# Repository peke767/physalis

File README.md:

# Physalis

The Physalis is 75% Keyboard.  

## Part List

PCB --- 1 pcs  
RP2040 Zero --- 1 pcs  
Diode [1N4148 SMD] --- 82 pcs  
Hotswap Socket --- 82 pcs  
Switch --- 82/81 pcs  
2u Stabilizer --- 3 pcs  
6.25u or 7u or 6u Stabilizer --- 1 pcs

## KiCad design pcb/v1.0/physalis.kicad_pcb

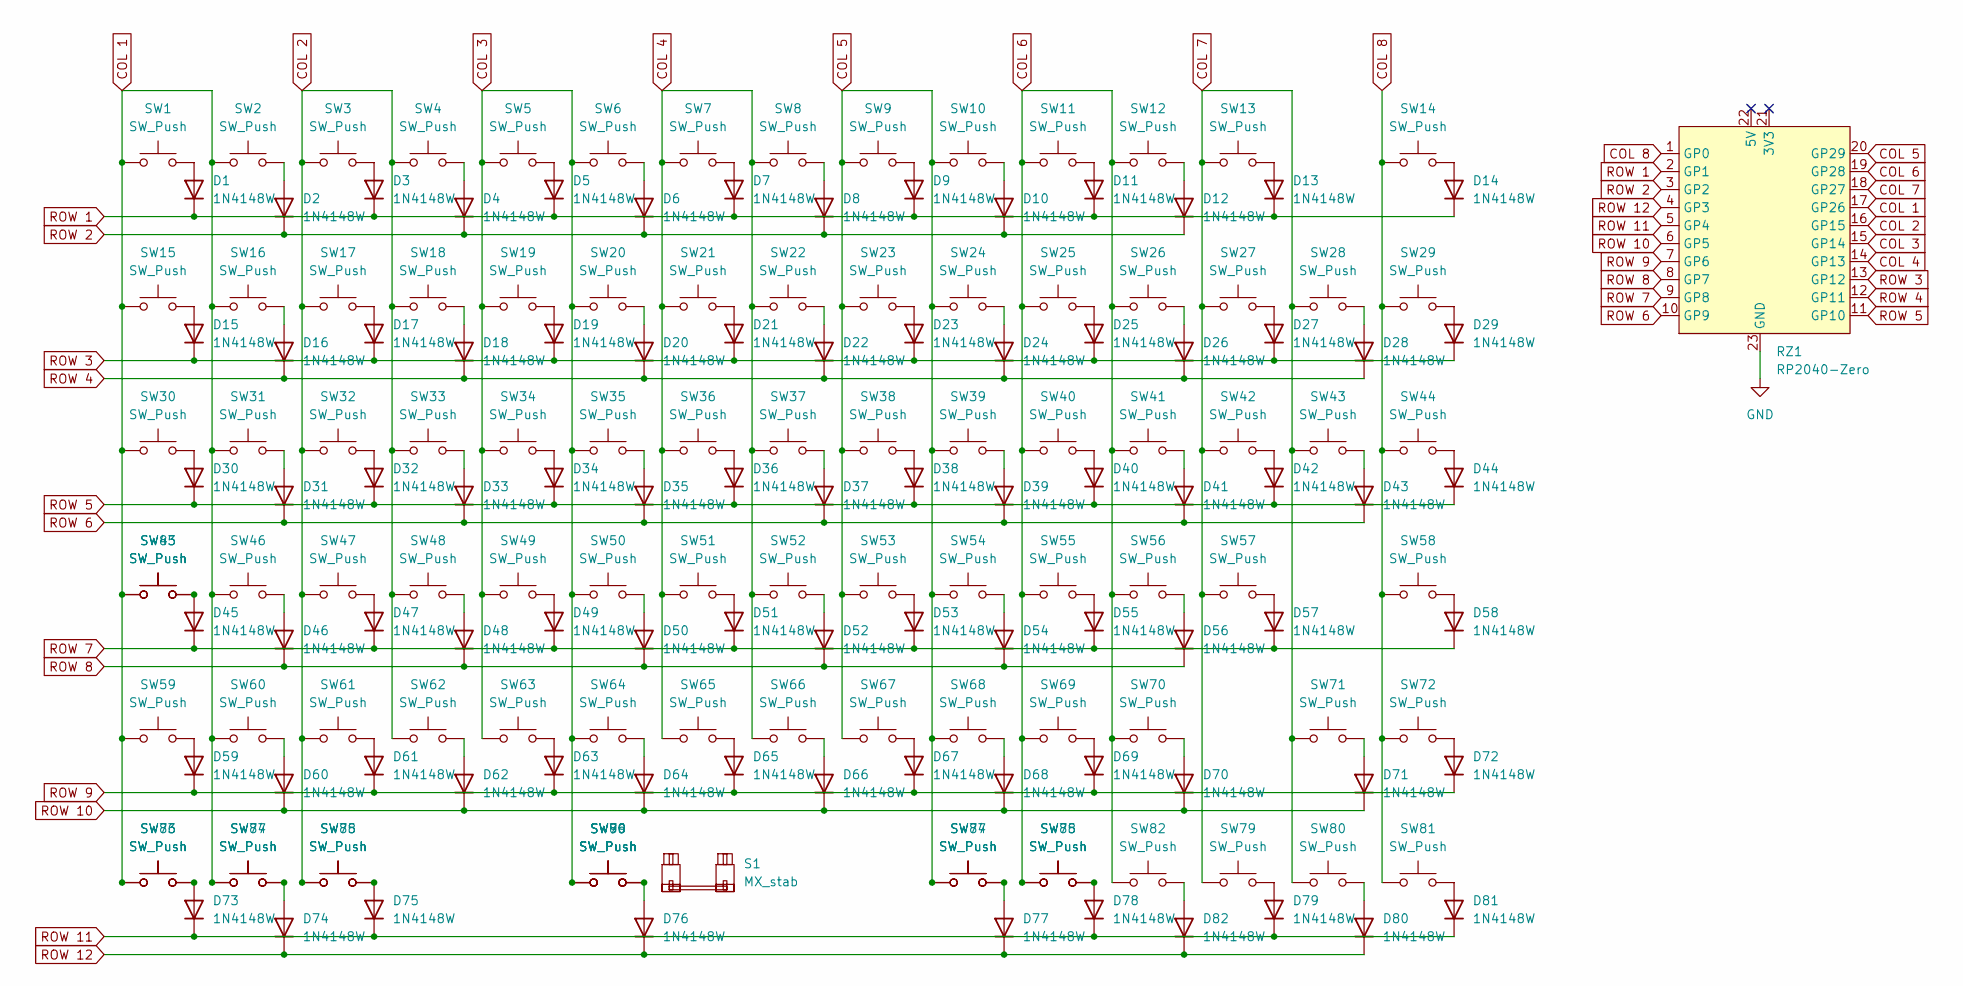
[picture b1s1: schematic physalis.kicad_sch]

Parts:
D1, D2, D3, D4, D5, D6, D7, D8, D9, D10, D11, D12, D13, D14, D15, D16, D17, D18, D19, D20, D21, D22, D23, D24, D25, D26, D27, D28, D29, D30, D31, D32, D33, D34, D35, D36, D37, D38, D39, D40, D41, D42, D43, D44, D45, D46, D47, D48, D49, D50, D51, D52, D53, D54, D55, D56, D57, D58, D59, D60, D61, D62, D63, D64, D65, D66, D67, D68, D69, D70, D71, D72, D73, D74, D75, D76, D77, D78, D79, D80, D81, D82: 1N4148W; D_SOD-123
RZ1: RP2040-Zero
S1: MX_stab; STAB_MX_6u
SW1, SW2, SW3, SW4, SW5, SW6, SW7, SW8, SW9, SW10, SW11, SW12, SW13, SW14, SW15, SW16, SW17, SW18, SW19, SW20, SW21, SW22, SW23, SW24, SW25, SW26, SW27, SW29, SW31, SW32, SW33, SW34, SW35, SW36, SW37, SW38, SW39, SW40, SW41, SW42, SW44, SW46, SW47, SW48, SW49, SW50, SW51, SW52, SW53, SW54, SW55, SW56, SW58, SW60, SW61, SW62, SW63, SW64, SW65, SW66, SW67, SW68, SW69, SW71, SW72, SW77, SW78, SW79, SW80, SW81, SW82, SW87, SW90: SW_Push; MX-Hotswap-1U
SW28: SW_Push; MX-Hotswap-2U
SW30, SW43, SW86, SW88: SW_Push; MX-Hotswap-1.5U
SW45, SW70: SW_Push; MX-Hotswap-1.75U
SW57, SW59: SW_Push; MX-Hotswap-2.25U
SW73, SW74, SW75, SW83, SW84, SW85: SW_Push; MX-Hotswap-1.25U
SW76: SW_Push; MX-Hotswap-6.25U
SW89: SW_Push; MX-Hotswap-7U-ReversedStabilizers

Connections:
COL 1: RZ1.17 (GP26), SW1.1, SW2.1, SW15.1, SW16.1, SW30.1, SW31.1, SW45.1, SW46.1, SW59.1, SW60.1, SW73.1, SW74.1, SW83.1, SW86.1, SW87.1
COL 2: RZ1.16 (GP15), SW3.1, SW4.1, SW17.1, SW18.1, SW32.1, SW33.1, SW47.1, SW48.1, SW61.1, SW62.1, SW75.1, SW88.1
COL 3: RZ1.15 (GP14), SW5.1, SW6.1, SW19.1, SW20.1, SW34.1, SW35.1, SW49.1, SW50.1, SW63.1, SW64.1, SW76.1, SW89.1, SW90.1
COL 4: RZ1.14 (GP13), SW7.1, SW8.1, SW21.1, SW22.1, SW36.1, SW37.1, SW51.1, SW52.1, SW65.1, SW66.1
COL 5: RZ1.20 (GP29), SW9.1, SW10.1, SW23.1, SW24.1, SW38.1, SW39.1, SW53.1, SW54.1, SW67.1, SW68.1, SW77.1, SW84.1
COL 6: RZ1.19 (GP28), SW11.1, SW12.1, SW25.1, SW26.1, SW40.1, SW41.1, SW55.1, SW56.1, SW69.1, SW70.1, SW78.1, SW82.1, SW85.1
COL 7: RZ1.18 (GP27), SW13.1, SW27.1, SW28.1, SW42.1, SW43.1, SW57.1, SW71.1, SW79.1, SW80.1
COL 8: RZ1.1 (GP0), SW14.1, SW29.1, SW44.1, SW58.1, SW72.1, SW81.1
GND: RZ1.23 (GND)
unnamed: D1.2 (A), SW1.2
unnamed: D2.2 (A), SW2.2
unnamed: D3.2 (A), SW3.2
unnamed: D4.2 (A), SW4.2
unnamed: D5.2 (A), SW5.2
unnamed: D6.2 (A), SW6.2
unnamed: D7.2 (A), SW7.2
unnamed: D8.2 (A), SW8.2
unnamed: D9.2 (A), SW9.2
unnamed: D10.2 (A), SW10.2
unnamed: D11.2 (A), SW11.2
unnamed: D12.2 (A), SW12.2
unnamed: D13.2 (A), SW13.2
unnamed: D14.2 (A), SW14.2
unnamed: D15.2 (A), SW15.2
unnamed: D16.2 (A), SW16.2
unnamed: D17.2 (A), SW17.2
unnamed: D18.2 (A), SW18.2
unnamed: D19.2 (A), SW19.2
unnamed: D20.2 (A), SW20.2
unnamed: D21.2 (A), SW21.2
unnamed: D22.2 (A), SW22.2
unnamed: D23.2 (A), SW23.2
unnamed: D24.2 (A), SW24.2
unnamed: D25.2 (A), SW25.2
unnamed: D26.2 (A), SW26.2
unnamed: D27.2 (A), SW27.2
unnamed: D28.2 (A), SW28.2
unnamed: D29.2 (A), SW29.2
unnamed: D30.2 (A), SW30.2
unnamed: D31.2 (A), SW31.2
unnamed: D32.2 (A), SW32.2
unnamed: D33.2 (A), SW33.2
unnamed: D34.2 (A), SW34.2
unnamed: D35.2 (A), SW35.2
unnamed: D36.2 (A), SW36.2
unnamed: D37.2 (A), SW37.2
unnamed: D38.2 (A), SW38.2
unnamed: D39.2 (A), SW39.2
unnamed: D40.2 (A), SW40.2
unnamed: D41.2 (A), SW41.2
unnamed: D42.2 (A), SW42.2
unnamed: D43.2 (A), SW43.2
unnamed: D44.2 (A), SW44.2
unnamed: D45.2 (A), SW45.2, SW83.2
unnamed: D46.2 (A), SW46.2
unnamed: D47.2 (A), SW47.2
unnamed: D48.2 (A), SW48.2
unnamed: D49.2 (A), SW49.2
unnamed: D50.2 (A), SW50.2
unnamed: D51.2 (A), SW51.2
unnamed: D52.2 (A), SW52.2
unnamed: D53.2 (A), SW53.2
unnamed: D54.2 (A), SW54.2
unnamed: D55.2 (A), SW55.2
unnamed: D56.2 (A), SW56.2
unnamed: D57.2 (A), SW57.2
unnamed: D58.2 (A), SW58.2
unnamed: D59.2 (A), SW59.2
unnamed: D60.2 (A), SW60.2
unnamed: D61.2 (A), SW61.2
unnamed: D62.2 (A), SW62.2
unnamed: D63.2 (A), SW63.2
unnamed: D64.2 (A), SW64.2
unnamed: D65.2 (A), SW65.2
unnamed: D66.2 (A), SW66.2
unnamed: D67.2 (A), SW67.2
unnamed: D68.2 (A), SW68.2
unnamed: D69.2 (A), SW69.2
unnamed: D70.2 (A), SW70.2
unnamed: D71.2 (A), SW71.2
unnamed: D72.2 (A), SW72.2
unnamed: D73.2 (A), SW73.2, SW86.2
unnamed: D74.2 (A), SW74.2, SW87.2
unnamed: D75.2 (A), SW75.2, SW88.2
unnamed: D76.2 (A), SW76.2, SW89.2, SW90.2
unnamed: D77.2 (A), SW77.2, SW84.2
unnamed: D78.2 (A), SW78.2, SW85.2
unnamed: D79.2 (A), SW79.2
unnamed: D80.2 (A), SW80.2
unnamed: D81.2 (A), SW81.2
unnamed: D82.2 (A), SW82.2
ROW 1: D1.1 (K), D3.1 (K), D5.1 (K), D7.1 (K), D9.1 (K), D11.1 (K), D13.1 (K), D14.1 (K), RZ1.2 (GP1)
ROW 2: D2.1 (K), D4.1 (K), D6.1 (K), D8.1 (K), D10.1 (K), D12.1 (K), RZ1.3 (GP2)
ROW 3: D15.1 (K), D17.1 (K), D19.1 (K), D21.1 (K), D23.1 (K), D25.1 (K), D27.1 (K), D29.1 (K), RZ1.13 (GP12)
ROW 4: D16.1 (K), D18.1 (K), D20.1 (K), D22.1 (K), D24.1 (K), D26.1 (K), D28.1 (K), RZ1.12 (GP11)
ROW 5: D30.1 (K), D32.1 (K), D34.1 (K), D36.1 (K), D38.1 (K), D40.1 (K), D42.1 (K), D44.1 (K), RZ1.11 (GP10)
ROW 6: D31.1 (K), D33.1 (K), D35.1 (K), D37.1 (K), D39.1 (K), D41.1 (K), D43.1 (K), RZ1.10 (GP9)
ROW 7: D45.1 (K), D47.1 (K), D49.1 (K), D51.1 (K), D53.1 (K), D55.1 (K), D57.1 (K), D58.1 (K), RZ1.9 (GP8)
ROW 8: D46.1 (K), D48.1 (K), D50.1 (K), D52.1 (K), D54.1 (K), D56.1 (K), RZ1.8 (GP7)
ROW 9: D59.1 (K), D61.1 (K), D63.1 (K), D65.1 (K), D67.1 (K), D69.1 (K), D72.1 (K), RZ1.7 (GP6)
ROW 10: D60.1 (K), D62.1 (K), D64.1 (K), D66.1 (K), D68.1 (K), D70.1 (K), D71.1 (K), RZ1.6 (GP5)
ROW 11: D73.1 (K), D75.1 (K), D78.1 (K), D79.1 (K), D81.1 (K), RZ1.5 (GP4)
ROW 12: D74.1 (K), D76.1 (K), D77.1 (K), D80.1 (K), D82.1 (K), RZ1.4 (GP3)

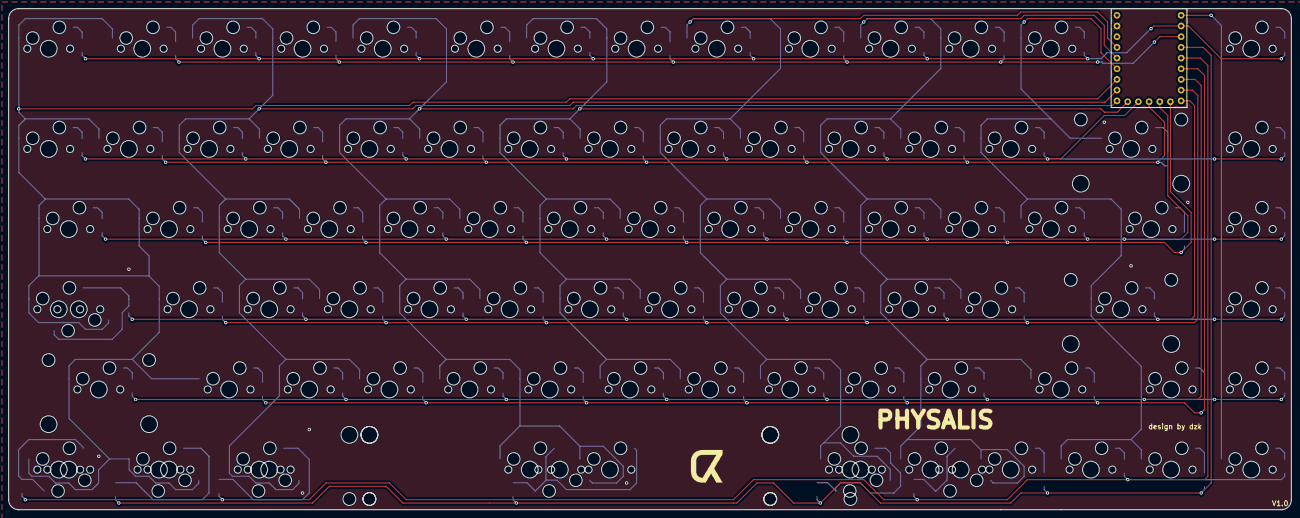
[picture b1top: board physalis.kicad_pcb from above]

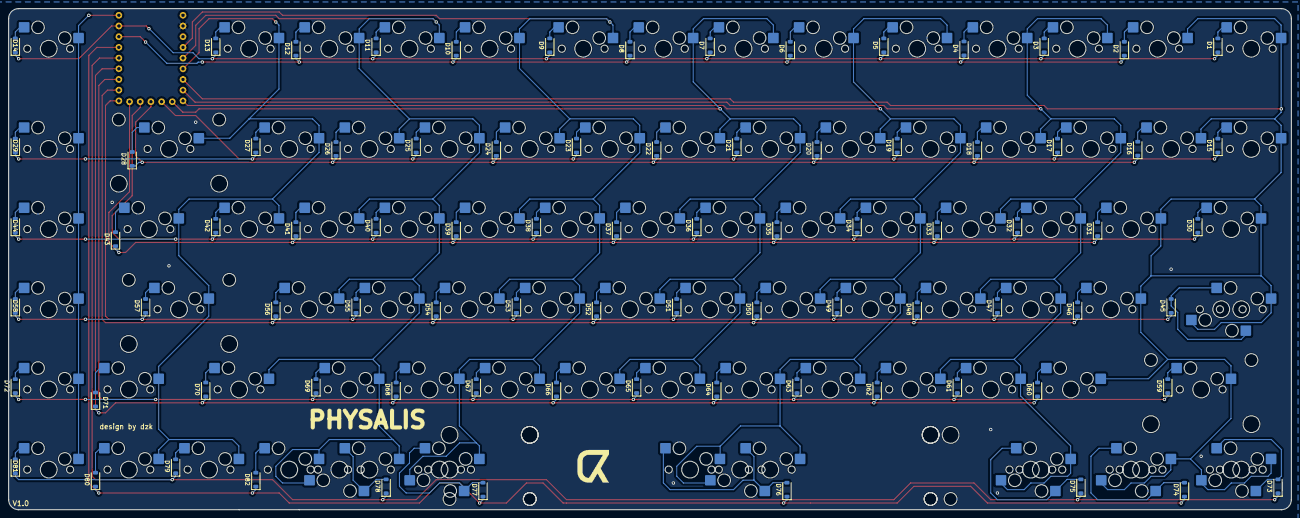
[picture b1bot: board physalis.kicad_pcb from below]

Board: 2 copper layers, 304.8 x 119.1 mm, 174 parts (82 on the bottom side), 102 nets.

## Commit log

2023-10-07 Create img
2023-12-11 Add files via upload
    fix error column
